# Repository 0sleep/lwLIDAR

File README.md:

# lwLIDAR

# Summary
lwLIDAR is a research project aiming to design, implement and test a low-cost compact 3D LiDAR for use in constrained robotics research. It consists of an array of 8 VL53L8CX 8x8 matrix LiDAR sensors mounted to a flexible PCB.

# Repository structure
This repository contains all required design files to construct and program a lwLIDAR sensor with an interface board to act as a sample implementation. Each subdirectory contains a more detailed README file.
- Flex - lwLIDAR core sensor PCB
- Rigid - interface board PCB
- Mechanical - 3D CAD files
- Firmware - example firmware to be run on interface board
- Software - example software to visualise live data

# Performance
|-------------------|-------------------------|
| Framerate         | 16 Hz                   |
| Maximum distance  | 4 m                     |
| Resolution        | 8 v x256 h              |
| FoV               | 45° v x 360° h          |
| Size              | 31x31x67 mm (with mast) |
| Weight            | 11g                     |
| Power consumption | 1.5W                    |
|-------------------|-------------------------|

# License
This project is licensed under the GNU AGPL license (see LICENSE.txt).

# Contributing
If you have improvements or want this repo to link to a usecase you made, please submit a pull request! If you have problems, please open an issue - I'm happy to improve this repository over time!

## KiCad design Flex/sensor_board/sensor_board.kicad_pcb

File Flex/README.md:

# Flex

This directory contains the KiCAD project files for the flexible PCB. It is only 8 VL53L8CX as well as an I2C GPIO expander. The stiffener layer should be 0.25mm polyimide to ensure the PCB (2 layer, 25um) fits in the molex connector [easy-on 1mm pitch 10 circuits](https://www.molex.com/en-us/products/part-detail/522071060). The PCB fits inside a 100mmx100mm square area to minimise PCB production costs. All passive components are hand-solderable 0603.

# Issues
The state of this directors is as-created for the thesis. This means that the I2C pullups are incorrectly set to pull up to VDD (3.3V), when they should be pulling to IOVDD (1.8V). To save production cost, only PI stiffeners are used. However, to provide better heat wicking from the sensors, it may be advisable to use stainless steel stiffeners behind the sensors. (Avoid stainless steel stiffener on the connector part, it will short out the connector!)

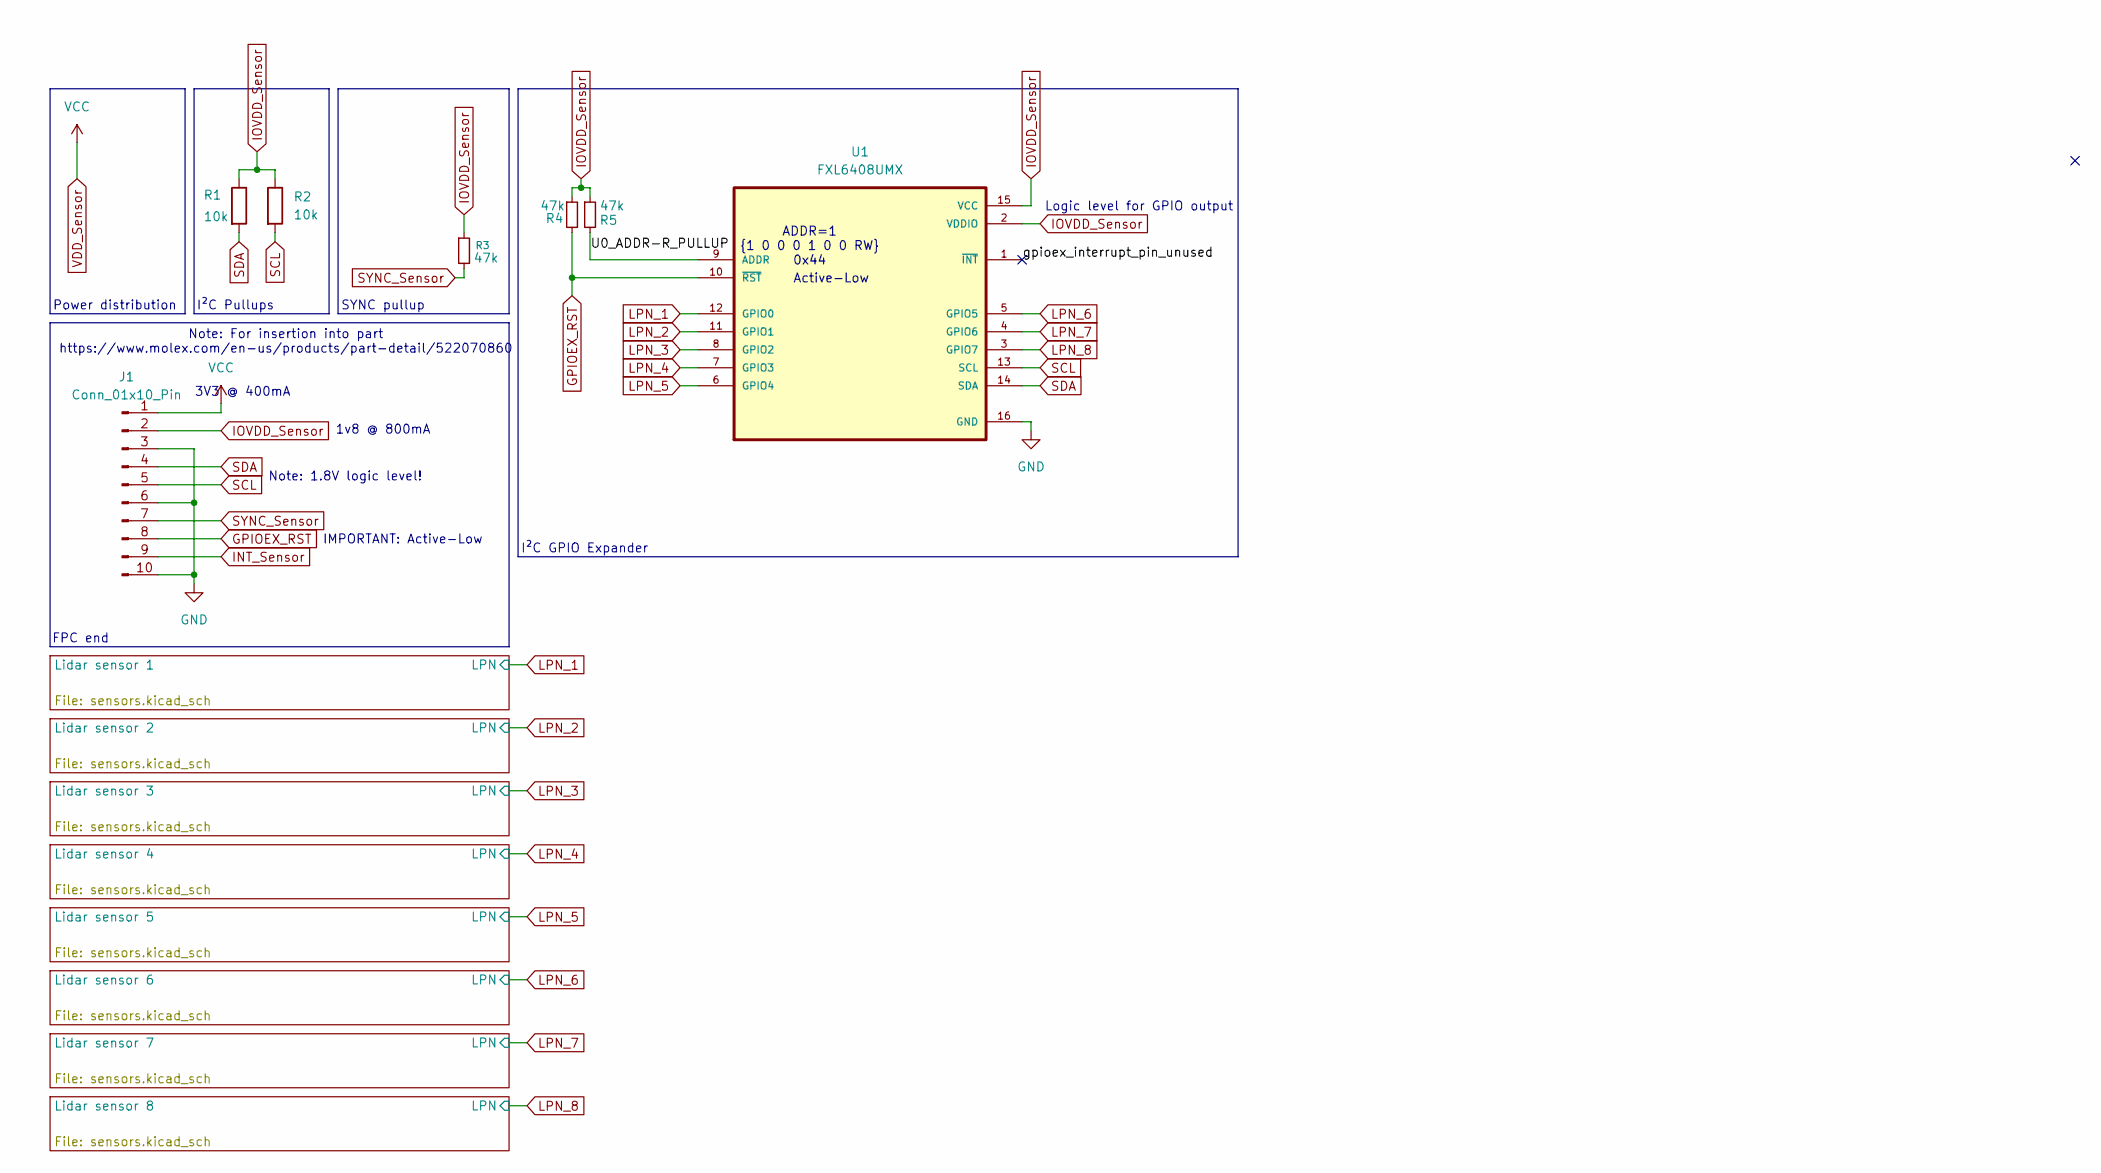
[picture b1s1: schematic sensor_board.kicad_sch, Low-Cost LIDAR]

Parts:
J1: Conn_01x10_Pin; Molex 10 Pin Flex 52207-1060
R1, R2: 10k; R_0603_1608Metric_Pad0.98x0.95mm_HandSolder
R3, R4, R5: 47k; R_0603_1608Metric_Pad0.98x0.95mm_HandSolder
U1: FXL6408UMX; QFN40P260X180X55-16N; PART_REV 1.0.0

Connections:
/U0_ADDR-R_PULLUP: R5.2, U1.9 (ADDR)
/gpioex_interrupt_pin_unused: U1.1 (~INT)
GND: J1.3, J1.6, J1.10, U1.16 (GND); also elsewhere on the board
GPIOEX_RST: J1.8, R4.2, U1.10 (~RST)
INT_Sensor: J1.9; also elsewhere on the board
IOVDD_Sensor: J1.2, R1.1, R2.1, R3.1, R4.1, R5.1, U1.2 (VDDIO), U1.15 (VCC); also elsewhere on the board
LPN_1: U1.12 (GPIO0); also elsewhere on the board
LPN_2: U1.11 (GPIO1); also elsewhere on the board
LPN_3: U1.8 (GPIO2); also elsewhere on the board
LPN_4: U1.7 (GPIO3); also elsewhere on the board
LPN_5: U1.6 (GPIO4); also elsewhere on the board
LPN_6: U1.5 (GPIO5); also elsewhere on the board
LPN_7: U1.4 (GPIO6); also elsewhere on the board
LPN_8: U1.3 (GPIO7); also elsewhere on the board
SCL: J1.5, R2.2, U1.13 (SCL); also elsewhere on the board
SDA: J1.4, R1.2, U1.14 (SDA); also elsewhere on the board
SYNC_Sensor: J1.7, R3.2; also elsewhere on the board
VDD_Sensor: J1.1; also elsewhere on the board

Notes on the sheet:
Logic level for GPIO output
Active-Low
Note: For insertion into part https://www.molex.com/en-us/products/part-detail/522070860
Note: 1.8V logic level!
I²C Pullups
IMPORTANT: Active-Low
ADDR=1 {1 0 0 0 1 0 0 RW} 0x44
Power distribution
SYNC pullup
FPC end
I²C GPIO Expander
1v8 @ 800mA
3V3 @ 400mA

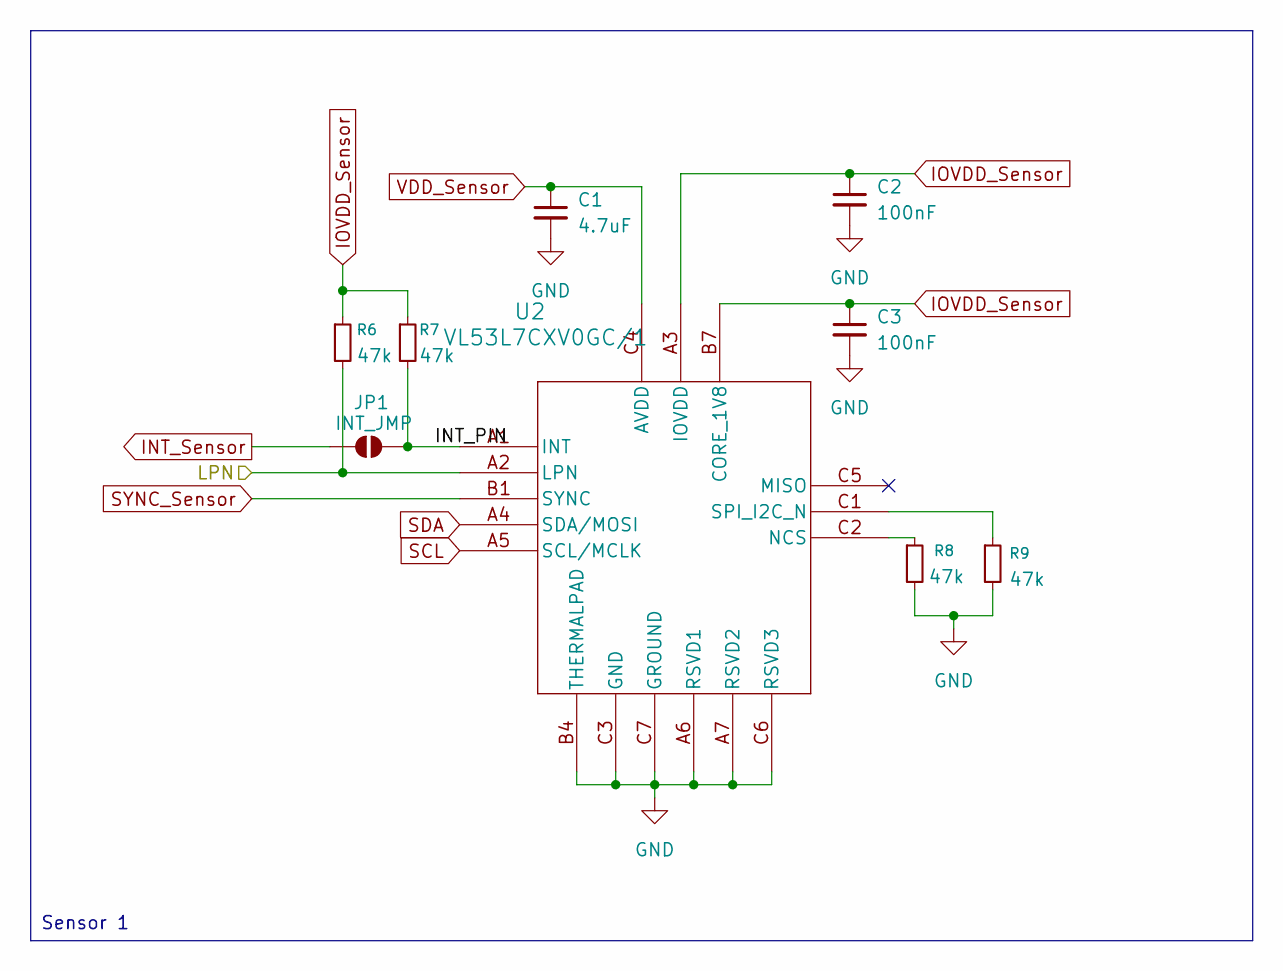
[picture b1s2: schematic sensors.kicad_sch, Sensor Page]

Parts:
C1: 4.7uF; C_0603_1608Metric_Pad1.08x0.95mm_HandSolder
C2, C3: 100nF; C_0603_1608Metric_Pad1.08x0.95mm_HandSolder
JP1: INT_JMP; C_0603_1608Metric_Pad1.08x0.95mm_HandSolder
R6, R7, R8, R9: 47k; R_0603_1608Metric_Pad0.98x0.95mm_HandSolder
U2: VL53L7CXV0GC/1; IC17_LGA16_STM

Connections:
/Lidar sensor 1/INT_PIN: JP1.2 (B), R7.2, U2.A1 (INT)
GND: C1.2, C2.2, C3.2, R8.2, R9.2, U2.A6 (RSVD1), U2.A7 (RSVD2), U2.B4 (THERMALPAD), U2.C3 (GND), U2.C6 (RSVD3), U2.C7 (GROUND); also elsewhere on the board
INT_Sensor: JP1.1 (A); also elsewhere on the board
IOVDD_Sensor: C2.1, C3.1, R6.1, R7.1, U2.A3 (IOVDD), U2.B7 (CORE_1V8); also elsewhere on the board
LPN_1: R6.2, U2.A2 (LPN); also elsewhere on the board
unnamed: R8.1, U2.C2 (NCS)
unnamed: R9.1, U2.C1 (SPI_I2C_N)
SCL: U2.A5 (SCL/MCLK); also elsewhere on the board
SDA: U2.A4 (SDA/MOSI); also elsewhere on the board
SYNC_Sensor: U2.B1 (SYNC); also elsewhere on the board
VDD_Sensor: C1.1, U2.C4 (AVDD); also elsewhere on the board

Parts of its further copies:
C4, C7, C10, C13, C16, C19, C22: 4.7uF; C_0603_1608Metric_Pad1.08x0.95mm_HandSolder
C5, C6, C8, C9, C11, C12, C14, C15, C17, C18, C20, C21, C23, C24: 100nF; C_0603_1608Metric_Pad1.08x0.95mm_HandSolder
JP2, JP3, JP4, JP5, JP6, JP7, JP8: INT_JMP; C_0603_1608Metric_Pad1.08x0.95mm_HandSolder
R10, R11, R12, R13, R14, R15, R16, R17, R18, R19, R20, R21, R22, R23, R24, R25, R26, R27, R28, R29, R30, R31, R32, R33, R34, R35, R36, R37: 47k; R_0603_1608Metric_Pad0.98x0.95mm_HandSolder
U3, U4, U5, U6, U7, U8, U9: VL53L7CXV0GC/1; IC17_LGA16_STM

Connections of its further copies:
/Lidar sensor 2/INT_PIN: JP2.2 (B), R11.2, U3.A1 (INT)
/Lidar sensor 3/INT_PIN: JP3.2 (B), R15.2, U4.A1 (INT)
/Lidar sensor 4/INT_PIN: JP4.2 (B), R19.2, U5.A1 (INT)
/Lidar sensor 5/INT_PIN: JP5.2 (B), R23.2, U6.A1 (INT)
/Lidar sensor 6/INT_PIN: JP6.2 (B), R27.2, U7.A1 (INT)
/Lidar sensor 7/INT_PIN: JP7.2 (B), R31.2, U8.A1 (INT)
/Lidar sensor 8/INT_PIN: JP8.2 (B), R35.2, U9.A1 (INT)
GND: C4.2, C5.2, C6.2, C7.2, C8.2, C9.2, C10.2, C11.2, C12.2, C13.2, C14.2, C15.2, C16.2, C17.2, C18.2, C19.2, C20.2, C21.2, C22.2, C23.2, C24.2, R12.2, R13.2, R16.2, R17.2, R20.2, R21.2, R24.2, R25.2, R28.2, R29.2, R32.2, R33.2, R36.2, R37.2, U3.A6 (RSVD1), U3.A7 (RSVD2), U3.B4 (THERMALPAD), U3.C3 (GND), U3.C6 (RSVD3), U3.C7 (GROUND), U4.A6 (RSVD1), U4.A7 (RSVD2), U4.B4 (THERMALPAD), U4.C3 (GND), U4.C6 (RSVD3), U4.C7 (GROUND), U5.A6 (RSVD1), U5.A7 (RSVD2), U5.B4 (THERMALPAD), U5.C3 (GND), U5.C6 (RSVD3), U5.C7 (GROUND), U6.A6 (RSVD1), U6.A7 (RSVD2), U6.B4 (THERMALPAD), U6.C3 (GND), U6.C6 (RSVD3), U6.C7 (GROUND), U7.A6 (RSVD1), U7.A7 (RSVD2), U7.B4 (THERMALPAD), U7.C3 (GND), U7.C6 (RSVD3), U7.C7 (GROUND), U8.A6 (RSVD1), U8.A7 (RSVD2), U8.B4 (THERMALPAD), U8.C3 (GND), U8.C6 (RSVD3), U8.C7 (GROUND), U9.A6 (RSVD1), U9.A7 (RSVD2), U9.B4 (THERMALPAD), U9.C3 (GND), U9.C6 (RSVD3), U9.C7 (GROUND); also elsewhere on the board
INT_Sensor: JP2.1 (A), JP3.1 (A), JP4.1 (A), JP5.1 (A), JP6.1 (A), JP7.1 (A), JP8.1 (A); also elsewhere on the board
IOVDD_Sensor: C5.1, C6.1, C8.1, C9.1, C11.1, C12.1, C14.1, C15.1, C17.1, C18.1, C20.1, C21.1, C23.1, C24.1, R10.1, R11.1, R14.1, R15.1, R18.1, R19.1, R22.1, R23.1, R26.1, R27.1, R30.1, R31.1, R34.1, R35.1, U3.A3 (IOVDD), U3.B7 (CORE_1V8), U4.A3 (IOVDD), U4.B7 (CORE_1V8), U5.A3 (IOVDD), U5.B7 (CORE_1V8), U6.A3 (IOVDD), U6.B7 (CORE_1V8), U7.A3 (IOVDD), U7.B7 (CORE_1V8), U8.A3 (IOVDD), U8.B7 (CORE_1V8), U9.A3 (IOVDD), U9.B7 (CORE_1V8); also elsewhere on the board
LPN_2: R10.2, U3.A2 (LPN); also elsewhere on the board
LPN_3: R14.2, U4.A2 (LPN); also elsewhere on the board
LPN_4: R18.2, U5.A2 (LPN); also elsewhere on the board
LPN_5: R22.2, U6.A2 (LPN); also elsewhere on the board
LPN_6: R26.2, U7.A2 (LPN); also elsewhere on the board
LPN_7: R30.2, U8.A2 (LPN); also elsewhere on the board
LPN_8: R34.2, U9.A2 (LPN); also elsewhere on the board
unnamed: R12.1, U3.C2 (NCS)
unnamed: R13.1, U3.C1 (SPI_I2C_N)
unnamed: R16.1, U4.C2 (NCS)
unnamed: R17.1, U4.C1 (SPI_I2C_N)
unnamed: R20.1, U5.C2 (NCS)
unnamed: R21.1, U5.C1 (SPI_I2C_N)
unnamed: R24.1, U6.C2 (NCS)
unnamed: R25.1, U6.C1 (SPI_I2C_N)
unnamed: R28.1, U7.C2 (NCS)
unnamed: R29.1, U7.C1 (SPI_I2C_N)
unnamed: R32.1, U8.C2 (NCS)
unnamed: R33.1, U8.C1 (SPI_I2C_N)
unnamed: R36.1, U9.C2 (NCS)
unnamed: R37.1, U9.C1 (SPI_I2C_N)
SCL: U3.A5 (SCL/MCLK), U4.A5 (SCL/MCLK), U5.A5 (SCL/MCLK), U6.A5 (SCL/MCLK), U7.A5 (SCL/MCLK), U8.A5 (SCL/MCLK), U9.A5 (SCL/MCLK); also elsewhere on the board
SDA: U3.A4 (SDA/MOSI), U4.A4 (SDA/MOSI), U5.A4 (SDA/MOSI), U6.A4 (SDA/MOSI), U7.A4 (SDA/MOSI), U8.A4 (SDA/MOSI), U9.A4 (SDA/MOSI); also elsewhere on the board
SYNC_Sensor: U3.B1 (SYNC), U4.B1 (SYNC), U5.B1 (SYNC), U6.B1 (SYNC), U7.B1 (SYNC), U8.B1 (SYNC), U9.B1 (SYNC); also elsewhere on the board
VDD_Sensor: C4.1, C7.1, C10.1, C13.1, C16.1, C19.1, C22.1, U3.C4 (AVDD), U4.C4 (AVDD), U5.C4 (AVDD), U6.C4 (AVDD), U7.C4 (AVDD), U8.C4 (AVDD), U9.C4 (AVDD); also elsewhere on the board

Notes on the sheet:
Sensor 1

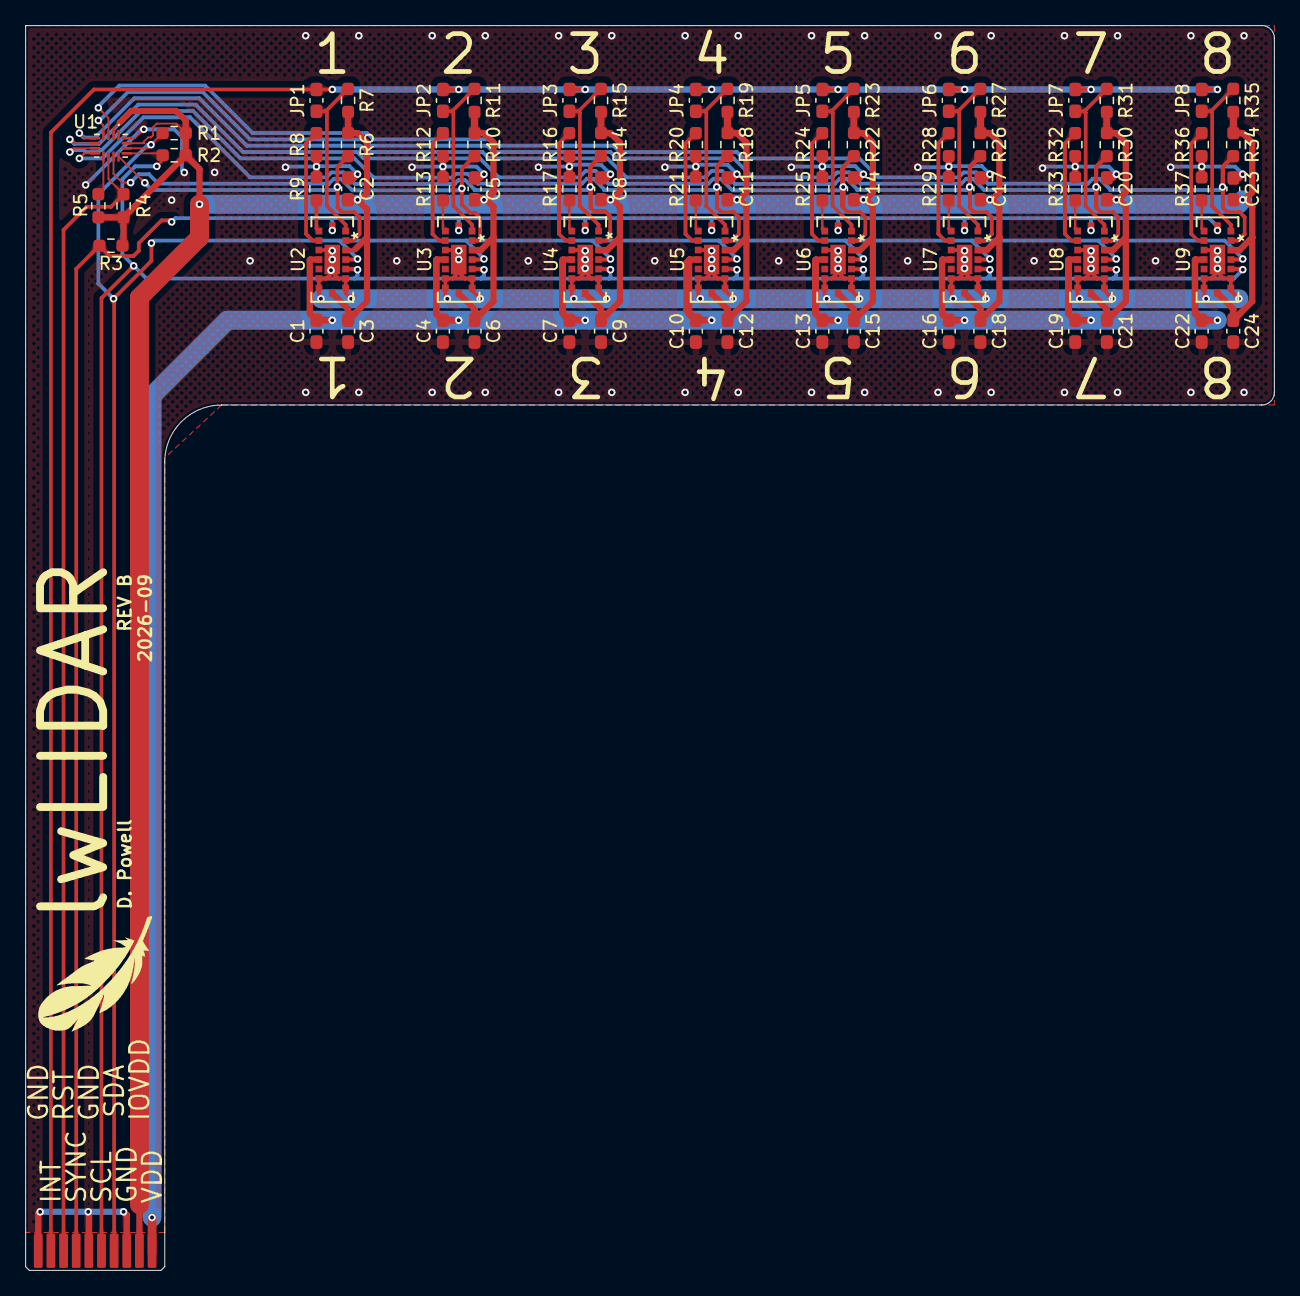
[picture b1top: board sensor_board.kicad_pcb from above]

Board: 2 copper layers, 98.8 x 98.4 mm, 79 parts (0 on the bottom side), 41 nets.

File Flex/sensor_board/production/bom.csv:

Designator,Footprint,Quantity,Value,LCSC Part #
"C1, C10, C13, C16, C19, C22, C4, C7",0603,8,4.7uF,
"C11, C12, C14, C15, C17, C18, C2, C20, C21, C23, C24, C3, C5, C6, C8, C9",0603,16,100nF,
J1,Molex 10 Pin Flex 52207-1060,1,Conn_01x10_Pin,
"R1, R2",0603,2,10k,
"R10, R11, R12, R13, R14, R15, R16, R17, R18, R19, R20, R21, R22, R23, R24, R25, R26, R27, R28, R29, R3, R30, R31, R32, R33, R34, R35, R36, R37, R4, R5, R6, R7, R8, R9",0603,35,47k,
U1,QFN40P260X180X55-16N,1,FXL6408UMX,
"U2, U3, U4, U5, U6, U7, U8, U9",IC17_LGA16_STM,8,VL53L7CXV0GC/1,

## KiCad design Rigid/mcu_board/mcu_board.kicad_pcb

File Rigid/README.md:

# FR4

This repo contains the rigid part of the lwLIDAR system. It is intended to act as a sample interface design. In a "proper" application, the functionality provided by this board would be implemented as part of the main device (e.g. on a small drone, this would be handled on the drone motherboard.)

# Features
This component provides a power and data interface to the flex PCB, a microcontroller to demonstrate functionality, as well as auxiliary components. The microcontroller is an esp32-s3 module, which allows wireless data streaming and simple USB programming.

Required for sensor operation:
- 3.3V power supply
- 1.8V logic power supply
- I2C bus (400kHz, 1.8V)
- interrupt pin to MCU @ 1.8V
- sync pin to flex PCB @ 1.8V

Additionally:
- Accelerometer / Gyro
- Magnetometer
- TP4056 BMS w/ automatic power switching
- QUIIC port

# Issues
- Power supply is based on low-dropout regulators. During operation, these will get very hot. Ideally, this would be implemented with a switching buck converter.
- No reset button (only boot button), which makes recovery of the esp32 annoying.
- No polarity markings on the battery connector. JST 2-pin battery polarity is NOT STANDARDISED!
- No facility to monitor battery voltage.

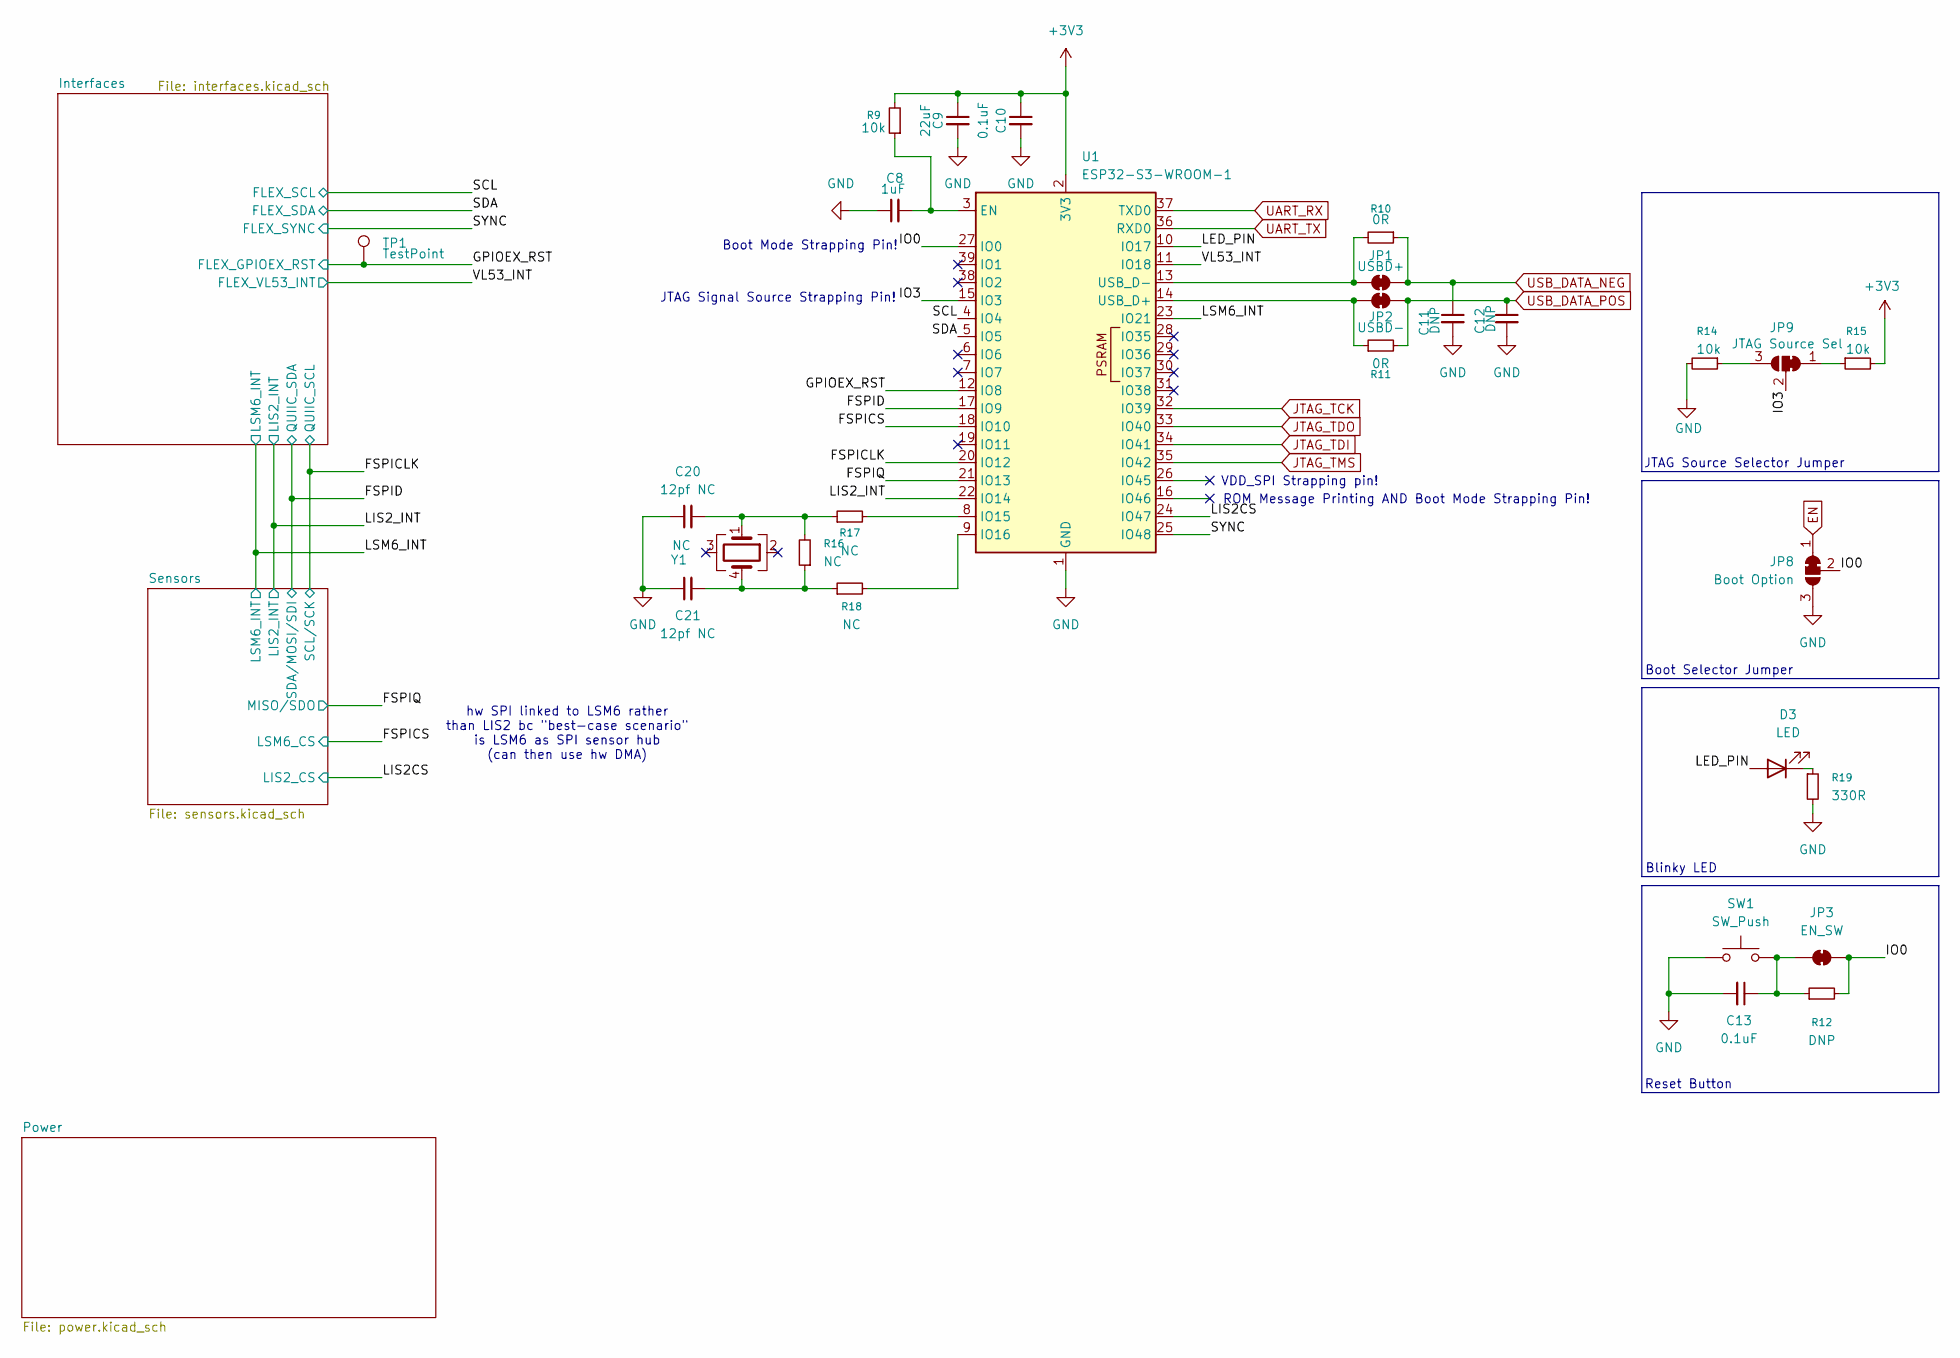
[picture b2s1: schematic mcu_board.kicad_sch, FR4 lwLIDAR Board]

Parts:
C8: 1uF; C_0603_1608Metric_Pad1.08x0.95mm_HandSolder
C9: 22uF; C_0603_1608Metric_Pad1.08x0.95mm_HandSolder
C10, C13: 0.1uF; C_0603_1608Metric_Pad1.08x0.95mm_HandSolder
C11, C12: DNP; C_0603_1608Metric_Pad1.08x0.95mm_HandSolder
C20, C21: 12pf NC; C_0603_1608Metric_Pad1.08x0.95mm_HandSolder
D3: LED; LED_0603_1608Metric_Pad1.05x0.95mm_HandSolder
JP1: USBD+; SolderJumper-2_P1.3mm_Bridged_RoundedPad1.0x1.5mm
JP2: USBD-; SolderJumper-2_P1.3mm_Bridged_RoundedPad1.0x1.5mm
JP3: EN_SW; SolderJumper-2_P1.3mm_Bridged2Bar_RoundedPad1.0x1.5mm
JP8: Boot Option; SolderJumper-3_P1.3mm_Bridged12_RoundedPad1.0x1.5mm
JP9: JTAG Source Sel; SolderJumper-3_P1.3mm_Bridged12_RoundedPad1.0x1.5mm
R9, R14, R15: 10k; R_0603_1608Metric_Pad0.98x0.95mm_HandSolder
R10, R11: 0R; R_0603_1608Metric_Pad0.98x0.95mm_HandSolder
R12: DNP; R_0603_1608Metric_Pad0.98x0.95mm_HandSolder
R16, R17, R18: NC; R_0603_1608Metric_Pad0.98x0.95mm_HandSolder
R19: 330R; R_0603_1608Metric_Pad0.98x0.95mm_HandSolder
SW1: SW_Push; SW_Push_1P1T_NO_CK_KMR2
TP1: TestPoint; TestPoint_Pad_D1.0mm
U1: ESP32-S3-WROOM-1
Y1: NC; Crystal_SMD_SeikoEpson_MC306-4Pin_8.0x3.2mm

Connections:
+3V3: C9.1, C10.1, R9.2, R15.2, U1.2 (3V3); also elsewhere on the board
/FSPICLK: U1.20 (IO12); also elsewhere on the board
/FSPICS: U1.18 (IO10); also elsewhere on the board
/FSPID: U1.17 (IO9); also elsewhere on the board
/FSPIQ: U1.21 (IO13); also elsewhere on the board
/GPIOEX_RST: TP1.1, U1.12 (IO8); also elsewhere on the board
/IO0: JP3.2 (B), JP8.2 (C), R12.2, U1.27 (IO0)
/IO3: JP9.2 (C), U1.15 (IO3)
/LED_PIN: D3.2 (A), U1.10 (IO17)
/LIS2CS: U1.24 (IO47); also elsewhere on the board
/LIS2_INT: U1.22 (IO14); also elsewhere on the board
/LSM6_INT: U1.23 (IO21); also elsewhere on the board
/SCL: U1.4 (IO4); also elsewhere on the board
/SDA: U1.5 (IO5); also elsewhere on the board
/SYNC: U1.25 (IO48); also elsewhere on the board
/VL53_INT: U1.11 (IO18); also elsewhere on the board
EN: JP8.1 (A); also elsewhere on the board
GND: C8.1, C9.2, C10.2, C11.2, C12.2, C13.2, C20.1, C21.1, JP8.3 (B), R14.2, R19.2, SW1.1, U1.1 (GND), U1.40 (GND), U1.41 (GND); also elsewhere on the board
JTAG_TCK: U1.32 (IO39); also elsewhere on the board
JTAG_TDI: U1.34 (IO41); also elsewhere on the board
JTAG_TDO: U1.33 (IO40); also elsewhere on the board
JTAG_TMS: U1.35 (IO42); also elsewhere on the board
unnamed: C20.2, R16.2, R17.1, Y1.1
unnamed: C21.2, R16.1, R18.1, Y1.4
unnamed: D3.1 (K), R19.1
unnamed: JP1.1 (A), R10.2, U1.13 (USB_D-)
unnamed: JP2.1 (A), R11.1, U1.14 (USB_D+)
unnamed: C13.1, JP3.1 (A), R12.1, SW1.2
unnamed: JP9.1 (A), R15.1
unnamed: JP9.3 (B), R14.1
unnamed: C8.2, R9.1, U1.3 (EN)
unnamed: R17.2, U1.8 (IO15)
unnamed: R18.2, U1.9 (IO16)
UART_RX: U1.37 (TXD0); also elsewhere on the board
UART_TX: U1.36 (RXD0); also elsewhere on the board
USB_DATA_NEG: C11.1, JP1.2 (B), R10.1; also elsewhere on the board
USB_DATA_POS: C12.1, JP2.2 (B), R11.2; also elsewhere on the board

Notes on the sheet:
ROM Message Printing AND Boot Mode Strapping Pin!
VDD_SPI Strapping pin!
Reset Button
JTAG Signal Source Strapping Pin!
hw SPI linked to LSM6 rather than LIS2 bc "best-case scenario" is LSM6 as SPI sensor hub (can then use hw DMA)
Boot Selector Jumper
JTAG Source Selector Jumper
Blinky LED
Boot Mode Strapping Pin!

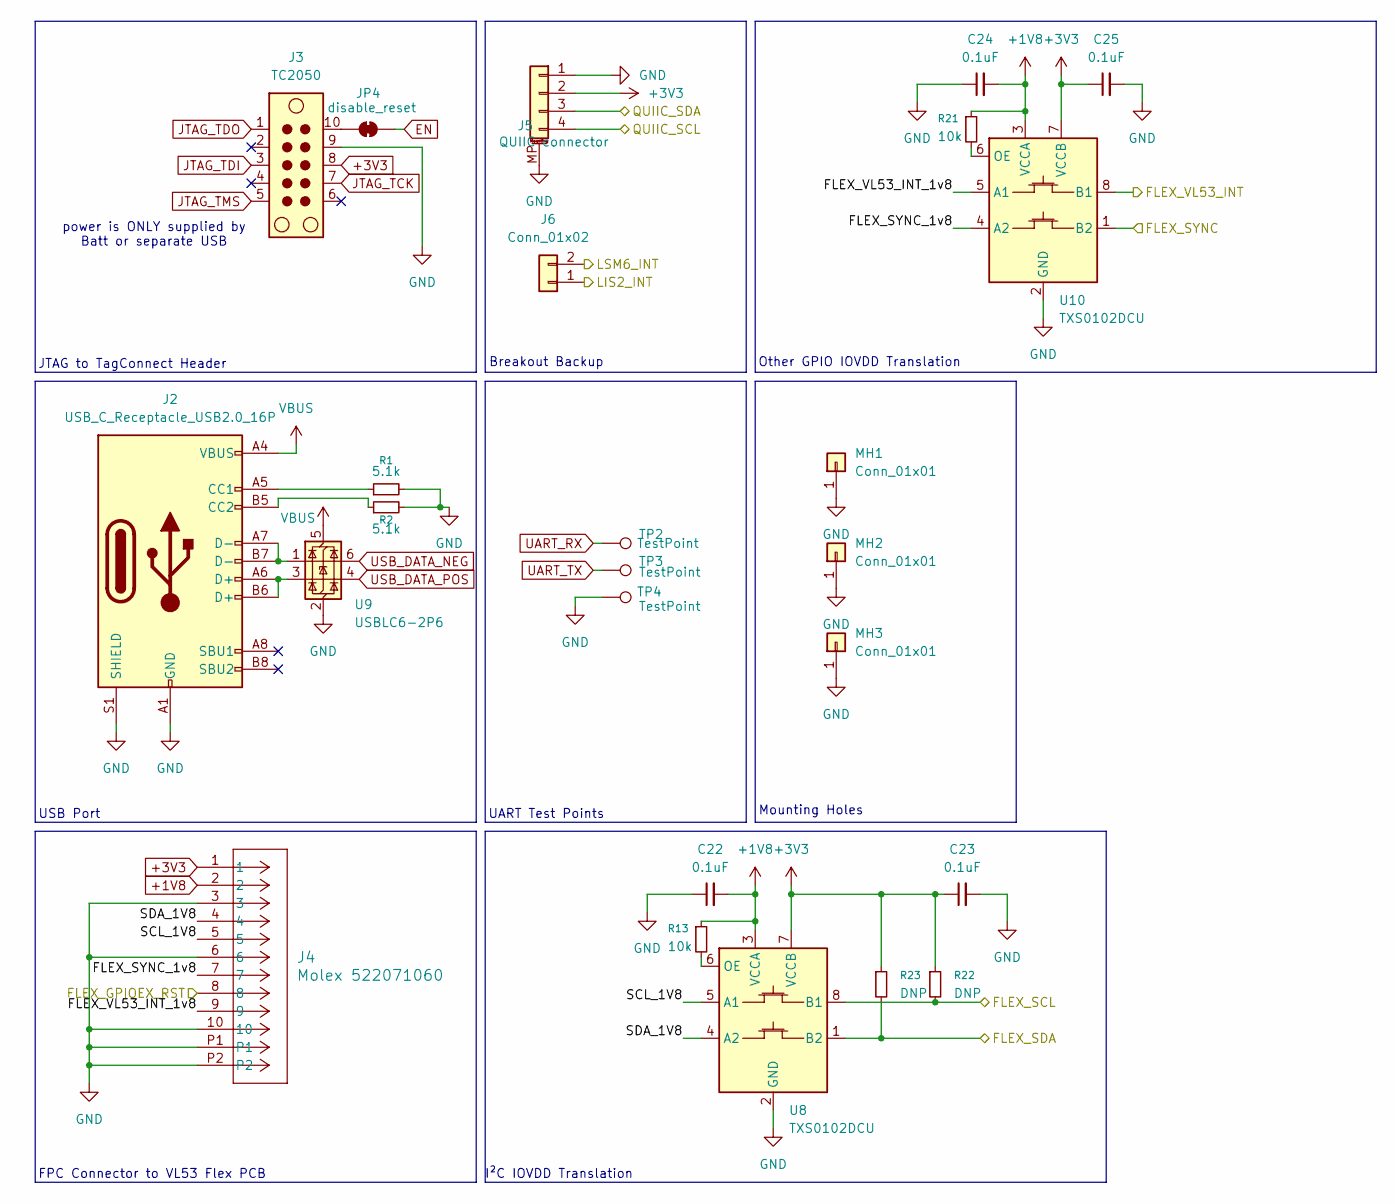
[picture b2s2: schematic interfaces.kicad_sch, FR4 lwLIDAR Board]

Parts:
C22, C23, C24, C25: 0.1uF; C_0603_1608Metric_Pad1.08x0.95mm_HandSolder
J2: USB_C_Receptacle_USB2.0_16P; USB_C_Receptacle_GCT_USB4105-xx-A_16P_TopMnt_Horizontal
J3: TC2050; Tag-Connect_TC2050-IDC-NL_2x05_P1.27mm_Vertical
J4: Molex 522071060; CON_522071060_MOL
J5: QUIIC connector; JST_SH_SM04B-SRSS-TB_1x04-1MP_P1.00mm_Horizontal
J6: Conn_01x02; PinHeader_1x02_P2.54mm_Vertical
JP4: disable_reset; SolderJumper-2_P1.3mm_Bridged_RoundedPad1.0x1.5mm
MH1, MH2, MH3: Conn_01x01; MountingHole_2.5mm_Pad_Via
R1, R2: 5.1k; R_0603_1608Metric_Pad0.98x0.95mm_HandSolder
R13, R21: 10k; R_0603_1608Metric_Pad0.98x0.95mm_HandSolder
R22, R23: DNP; R_0603_1608Metric_Pad0.98x0.95mm_HandSolder
TP2, TP3: TestPoint; TestPoint_Pad_D1.0mm
TP4: TestPoint; TestPoint_Pad_1.0x1.0mm
U8, U10: TXS0102DCU; VSSOP-8_2.3x2mm_P0.5mm
U9: USBLC6-2P6; SOT-666

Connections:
+1V8: C22.2, C24.2, J4.2, R13.1, R21.1, U8.3 (VCCA), U10.3 (VCCA); also elsewhere on the board
+3V3: C23.1, C25.1, J3.8, J4.1, J5.2, R22.1, R23.1, U8.7 (VCCB), U10.7 (VCCB); also elsewhere on the board
/FSPICLK: J5.4; also elsewhere on the board
/FSPID: J5.3; also elsewhere on the board
/GPIOEX_RST: J4.8; also elsewhere on the board
/Interfaces/FLEX_SYNC_1v8: J4.7, U10.4 (A2)
/Interfaces/FLEX_VL53_INT_1v8: J4.9, U10.5 (A1)
/Interfaces/SCL_1V8: J4.5, U8.5 (A1)
/Interfaces/SDA_1V8: J4.4, U8.4 (A2)
/LIS2_INT: J6.1; also elsewhere on the board
/LSM6_INT: J6.2; also elsewhere on the board
/SCL: R22.2, U8.8 (B1); also elsewhere on the board
/SDA: R23.2, U8.1 (B2); also elsewhere on the board
/SYNC: U10.1 (B2); also elsewhere on the board
/VL53_INT: U10.8 (B1); also elsewhere on the board
EN: JP4.1 (A); also elsewhere on the board
GND: C22.1, C23.2, C24.1, C25.2, J2.A1 (GND), J2.A12 (GND), J2.B1 (GND), J2.B12 (GND), J2.S1 (SHIELD), J3.9, J4.3, J4.6, J4.10, J4.P1, J4.P2, J5.1, J5.MP (MountPin), MH1.1, MH2.1, MH3.1, R1.2, R2.2, TP4.1, U8.2 (GND), U9.2 (GND), U10.2 (GND); also elsewhere on the board
JTAG_TCK: J3.7; also elsewhere on the board
JTAG_TDI: J3.3; also elsewhere on the board
JTAG_TDO: J3.1; also elsewhere on the board
JTAG_TMS: J3.5; also elsewhere on the board
unnamed: J2.A5 (CC1), R1.1
unnamed: J2.B5 (CC2), R2.1
unnamed: J2.A6 (D+), J2.B6 (D+), U9.3 (I/O2)
unnamed: J2.A7 (D-), J2.B7 (D-), U9.1 (I/O1)
unnamed: J3.10, JP4.2 (B)
unnamed: R13.2, U8.6 (OE)
unnamed: R21.2, U10.6 (OE)
USB_DATA_NEG: U9.6 (I/O1); also elsewhere on the board
USB_DATA_POS: U9.4 (I/O2); also elsewhere on the board
VBUS: J2.A4 (VBUS), J2.A9 (VBUS), J2.B4 (VBUS), J2.B9 (VBUS), U9.5 (VBUS); also elsewhere on the board

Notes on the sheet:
JTAG to TagConnect Header
Other GPIO IOVDD Translation
USB Port
FPC Connector to VL53 Flex PCB
power is ONLY supplied by Batt or separate USB
Mounting Holes
Breakout Backup
I²C IOVDD Translation
UART Test Points

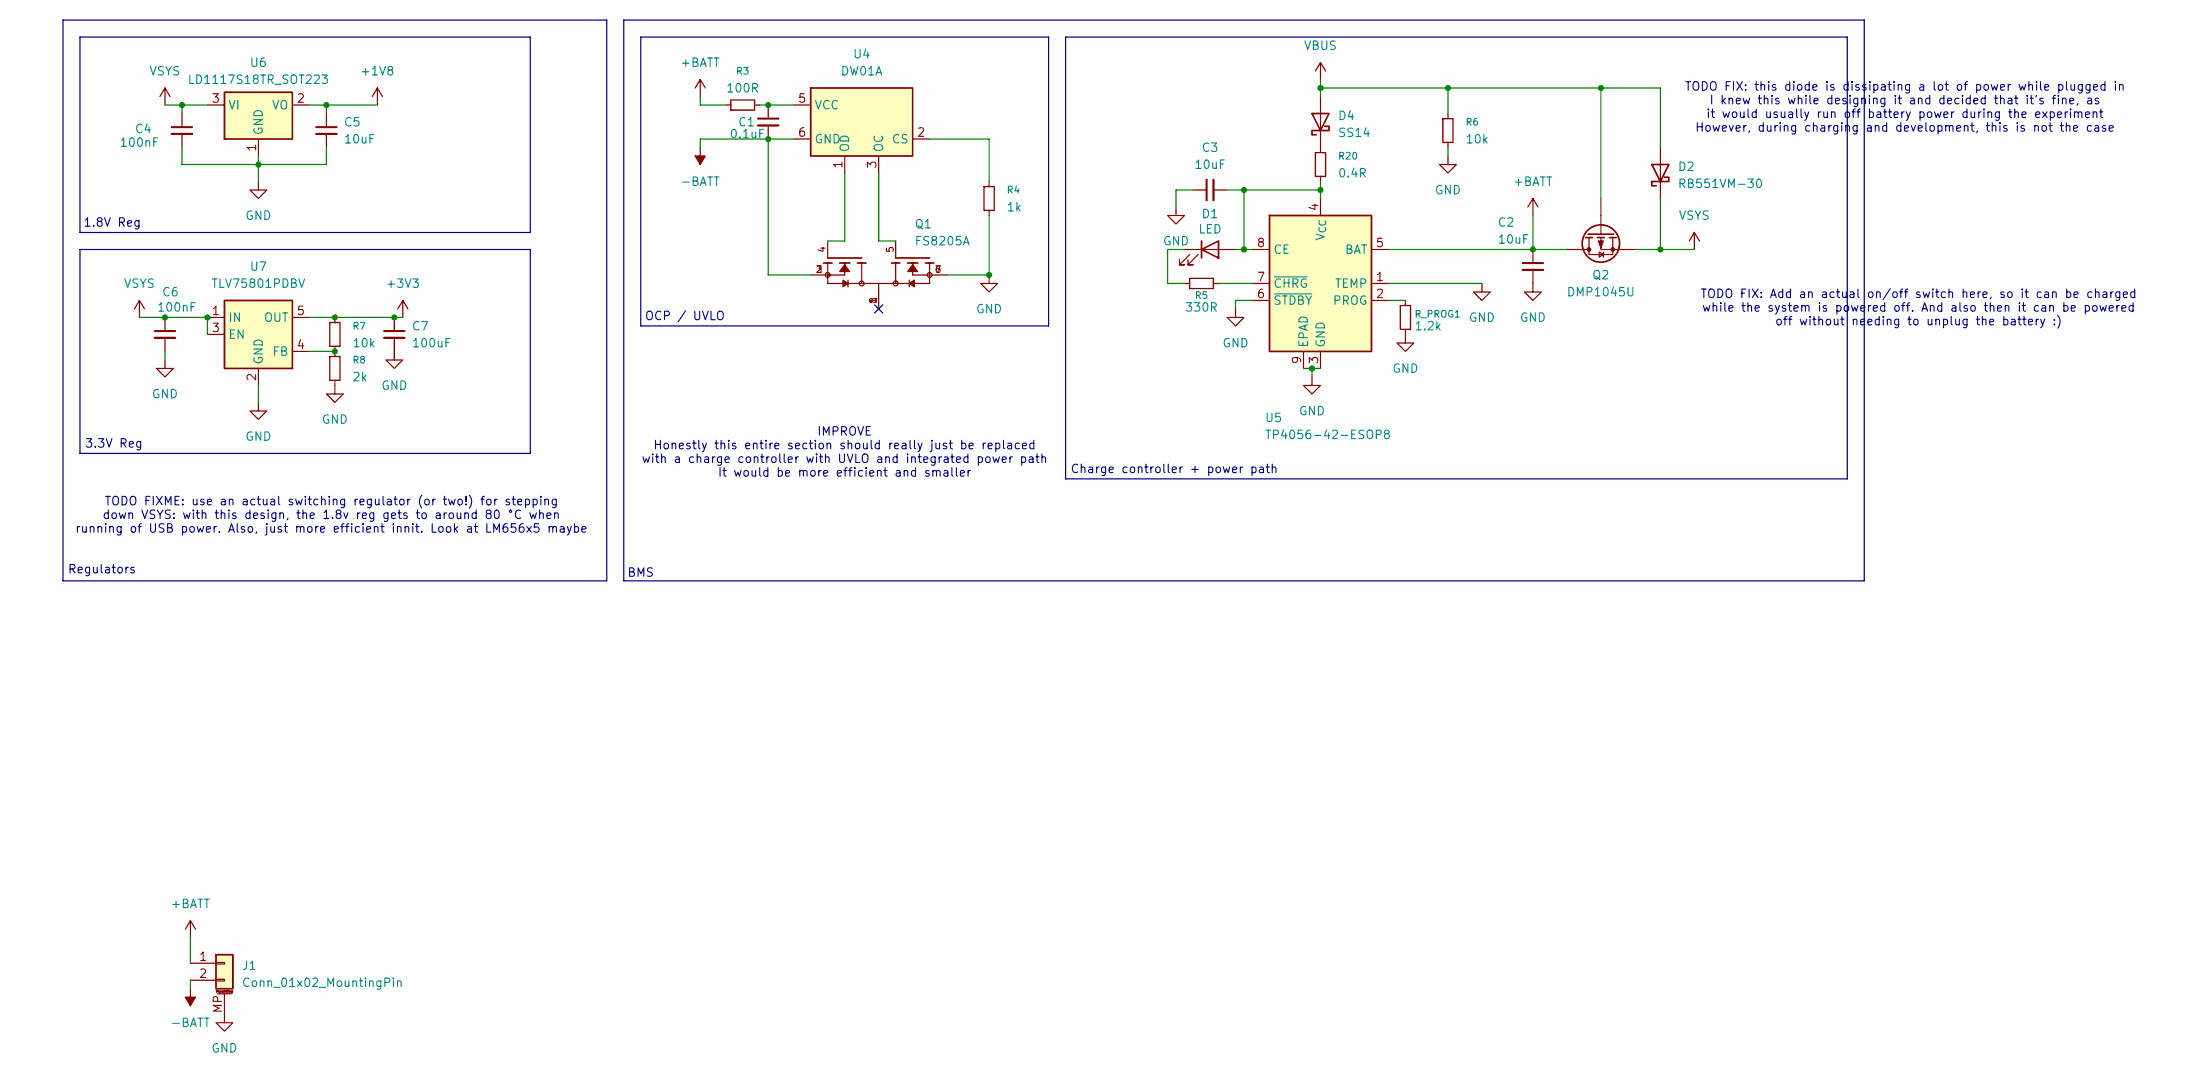
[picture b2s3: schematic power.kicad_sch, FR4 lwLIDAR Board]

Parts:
C1: 0.1uF; C_0603_1608Metric_Pad1.08x0.95mm_HandSolder
C2, C3, C5: 10uF; C_0603_1608Metric_Pad1.08x0.95mm_HandSolder
C4, C6: 100nF; C_0603_1608Metric_Pad1.08x0.95mm_HandSolder
C7: 100uF; C_0603_1608Metric_Pad1.08x0.95mm_HandSolder
D1: LED; LED_0603_1608Metric_Pad1.05x0.95mm_HandSolder
D2: RB551VM-30; DIO_RB500V_ROM
D4: SS14; DIOM5227X270N
J1: Conn_01x02_MountingPin; JST_PH_S2B-PH-SM4-TB_1x02-1MP_P2.00mm_Horizontal
Q1: FS8205A; SOP65P640X120-8N; PARTREV 1.7
Q2: DMP1045U; TSOT-23
R3: 100R; R_0603_1608Metric_Pad0.98x0.95mm_HandSolder
R4: 1k; R_0603_1608Metric_Pad0.98x0.95mm_HandSolder
R5: 330R; R_0603_1608Metric_Pad0.98x0.95mm_HandSolder
R6, R7: 10k; R_0603_1608Metric_Pad0.98x0.95mm_HandSolder
R8: 2k; R_0603_1608Metric_Pad0.98x0.95mm_HandSolder
R20: 0.4R; R_0603_1608Metric_Pad0.98x0.95mm_HandSolder
R_PROG1: 1.2k; R_0603_1608Metric_Pad0.98x0.95mm_HandSolder
U4: DW01A; SOT-23-6
U5: TP4056-42-ESOP8; SOIC-8-1EP_3.9x4.9mm_P1.27mm_EP2.41x3.3mm_ThermalVias
U6: LD1117S18TR_SOT223; SOT-223-3_TabPin2
U7: TLV75801PDBV; SOT-23-5

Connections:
+1V8: C5.1, U6.2 (VO); also elsewhere on the board
+3V3: C7.1, R7.1, U7.5 (OUT); also elsewhere on the board
+BATT: C2.1, J1.1, Q2.D, R3.1, U5.5 (BAT)
-BATT: C1.2, J1.2, Q1.2, Q1.3, U4.6 (GND)
GND: C2.2, C3.1, C4.2, C5.2, C6.2, C7.2, J1.MP (MountPin), Q1.6, Q1.7, R4.2, R6.2, R8.2, R_PROG1.2, U5.1 (TEMP), U5.3 (GND), U5.6 (~STDBY), U5.9 (EPAD), U6.1 (GND), U7.2 (GND); also elsewhere on the board
unnamed: C3.2, D1.2 (A), R20.2, U5.4 (V_{CC}), U5.8 (CE)
unnamed: D1.1 (K), R5.1
unnamed: D4.1 (K), R20.1
unnamed: R4.1, U4.2 (CS)
unnamed: Q1.5, U4.3 (OC)
unnamed: Q1.4, U4.1 (OD)
unnamed: C1.1, R3.2, U4.5 (VCC)
unnamed: R_PROG1.1, U5.2 (PROG)
unnamed: R5.2, U5.7 (~CHRG)
unnamed: R7.2, R8.1, U7.4 (FB)
VBUS: D2.2 (A), D4.2 (A), Q2.G, R6.1; also elsewhere on the board
VSYS: C4.1, C6.1, D2.1 (K), Q2.S, U6.3 (VI), U7.1 (IN), U7.3 (EN)

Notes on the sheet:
IMPROVE Honestly this entire section should really just be replaced with a charge controller with UVLO and integrated power path It would be more efficient and smaller
TODO FIX: Add an actual on/off switch here, so it can be charged while the system is powered off. And also then it can be powered off without needing to unplug the battery :)
3.3V Reg
OCP / UVLO
1.8V Reg
Regulators
TODO FIX: this diode is dissipating a lot of power while plugged in I knew this while designing it and decided that it's fine, as it would usually run off battery power during the experiment However, during charging and development, this is not the case
BMS
TODO FIXME: use an actual switching regulator (or two!) for stepping down VSYS: with this design, the 1.8v reg gets to around 80 °C when running of USB power. Also, just more efficient innit. Look at LM656x5 maybe
Charge controller + power path
